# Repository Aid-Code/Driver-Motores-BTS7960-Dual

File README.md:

# TitanCore 7960: Driver BTS7960 Dual Channel Custom
#### Buenas! Soy Aiden, y les quise escribir un pequeño texto para comentarles de este desarrollo que hice para mi robot y para la comunidad!

## Origen
La idea inicialmente empezó porque utilizaba un Monster Shield (VNH2SP30) que no suele ser tan fácil de conseguir, y quizás si se consigue es caro, por lo que necesitaba conseguir una alternativa a este driver de motores para mi robot Sumo.  
De ahí empecé a buscar como funcionaba un **Puente H**, que componentes se usaban, que transistores usar y por qué.   
Como primer acercamiento armé un Puente H con transistores mosfet en una placa experimental, usando gate drivers, que milagrosamente funcionó (después de revisar 50 veces mis dudosas soldaduras a las 5 A.M), pero cuando hice un primer diseño de la PCB, me di cuenta que no era lo suficientemente eficiente en espacio.
No importaba cuantos componentes SMD usara, era imposible reducirla.   
Más adelante, después de un tiempo de buscar (y charlar con mi LLM de confianza) encontré que existían encapsulados que integraban dos transistores "en uno". 
A todo esto, yo ya conocía el módulo comercial del BTS7960, pero me parecía una placa gigante (con un disipador gigante) para el uso que yo le quería dar. En esta parte de mi investigación descubrí que los BTS7960 eran esos peculiares encapsulados que integraban "dos transistores en uno". Por lo que dije PERFECTO, LOS COMPRO; LOS DESUELDO; ARMO MI PLACA!  
Dicho y hecho, acá estamos!

## Funcionamiento
La dinamica de este driver de motores es un poco distinta a lo habitual, comparandola con un Monster Shield o un L298n.  
Los pines son:
- GND
- VCC --> Voltaje lógico de 3.3v a 5v
- EN_1 --> Habilita el paso de corriente al Canal 1 (Opcional conectarlo a un pin, puede ir a VCC)
- EN_2 --> Habilita el paso de corriente al Canal 2 (Opcional conectarlo a un pin, puede ir a VCC)
- PWM_A --> Señal PWM del Canal 1 en una dirección
- PWM_B --> Señal PWM del Canal 1 en dirección contraria
- PWM_C --> Señal PWM del Canal 2 en una dirección
- PWM_D --> Señal PWM del Canal 2 en dirección contraria

- VS --> Voltaje de alimentación y salida a los motores de 6v a 28v (**Aprox. basado en la datasheet del BTS7960**)

## Puesto a prueba
Hasta ahora los parametros con los que puse a prueba el funcionamiento del driver son:  
- VCC: 5v
- VS: ~15v

La idea es utilizarlo a 24v con motores que podrían llegar a consumir 11,2A por canal. Cuando lo pruebe y confirme que no explota lo comento!

## Licencia y Uso Comercial
*Este proyecto está licenciado bajo* **Creative Commons Atribución-NoComercial-CompartirIgual 4.0 Internacional (CC BY-NC-SA 4.0)**. Consulta el archivo [LICENSE](LICENSE) para más detalles.
- *Puedes clonar, fabricar, estudiar y modificar este diseño libremente para proyectos personales, educativos o de competencia.*
- *Queda terminantemente prohibida la comercialización, venta directa o integración comercial de este diseño sin autorización previa.*
- Para consultas comerciales o adquisición de módulos ensamblados, contactar a: aiden.maidp@gmail.com

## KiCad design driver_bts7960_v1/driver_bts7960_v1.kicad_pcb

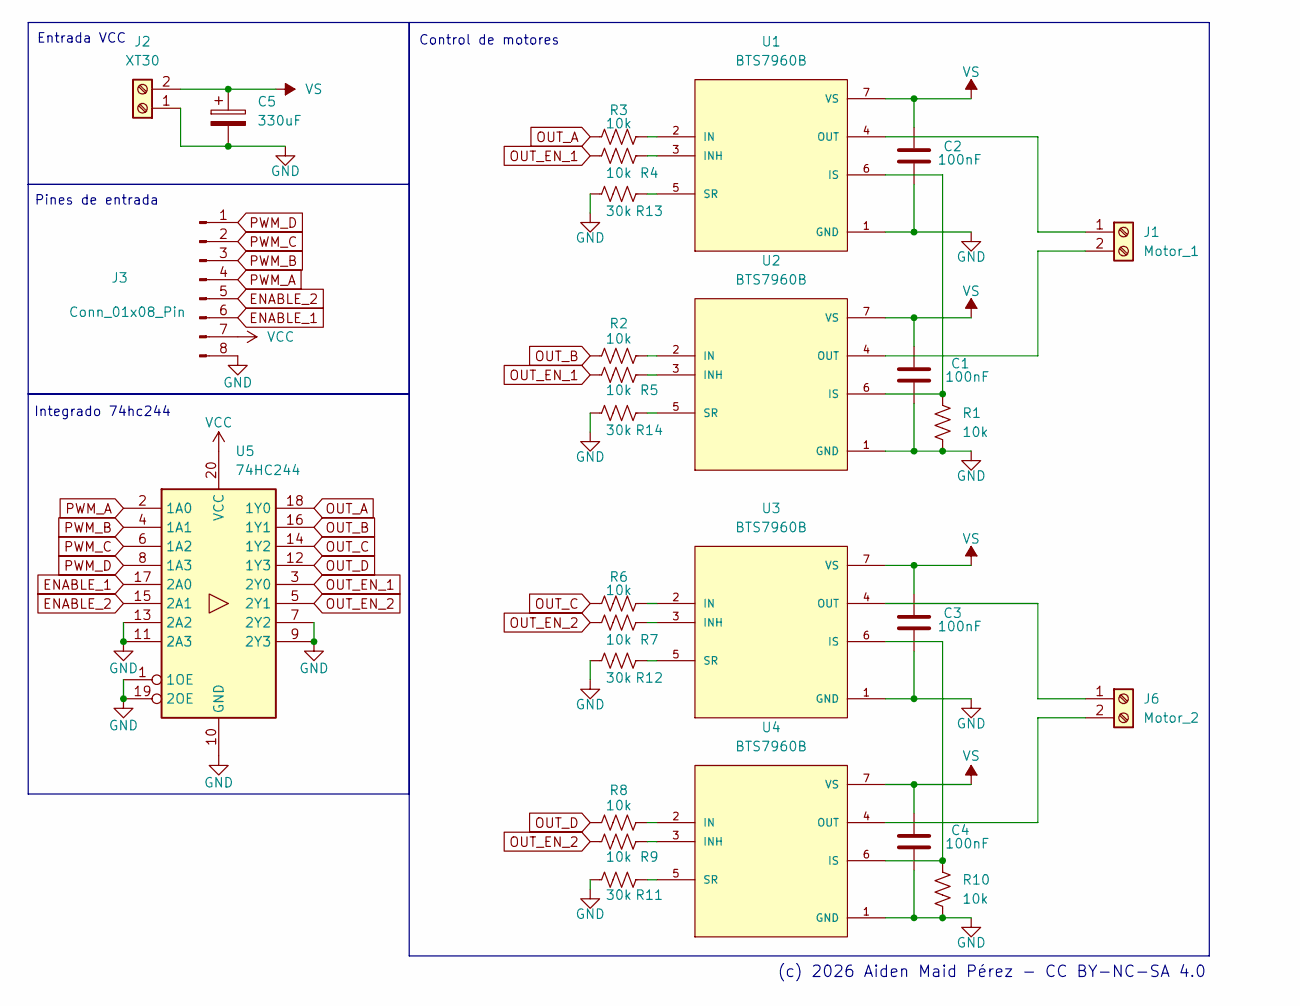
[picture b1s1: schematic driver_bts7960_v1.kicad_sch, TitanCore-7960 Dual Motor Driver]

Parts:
C1, C2, C3, C4: 100nF; C_0805_2012Metric_Pad1.18x1.45mm_HandSolder
C5: 330uF; CP_Radial_D8.0mm_P5.00mm
J1: Motor_1; AMASS_XT30U-F_1x02_P5.0mm_Vertical
J2: XT30; AMASS_XT30U-F_1x02_P5.0mm_Vertical
J3: Conn_01x08_Pin; PinHeader_1x08_P2.54mm_Vertical
J6: Motor_2; AMASS_XT30U-F_1x02_P5.0mm_Vertical
R1, R2, R3, R4, R5, R6, R7, R8, R9, R10: 10k; R_0805_2012Metric_Pad1.20x1.40mm_HandSolder
R11, R12, R13, R14: 30k; R_0805_2012Metric_Pad1.20x1.40mm_HandSolder
U1, U2, U3, U4: BTS7960B; BTS7960B_DPAK127P1490X440-8N; PARTREV 1.1
U5: 74HC244; SOIC127P1032X265-20N

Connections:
ENABLE_1: J3.6, U5.17 (2A0)
ENABLE_2: J3.5, U5.15 (2A1)
GND: C1.2, C2.2, C3.2, C4.2, C5.2, J2.1, J3.8, R1.2, R10.2, R11.2, R12.2, R13.2, R14.2, U1.1 (GND), U2.1 (GND), U3.1 (GND), U4.1 (GND), U5.1 (1OE), U5.7 (2Y2), U5.9 (2Y3), U5.10 (GND), U5.11 (2A3), U5.13 (2A2), U5.19 (2OE)
unnamed: J1.1, U1.4 (OUT), U1.8 (OUT)
unnamed: J1.2, U2.4 (OUT), U2.8 (OUT)
unnamed: J6.1, U3.4 (OUT), U3.8 (OUT)
unnamed: J6.2, U4.4 (OUT), U4.8 (OUT)
unnamed: R3.1, U1.2 (IN)
unnamed: R4.1, U1.3 (INH)
unnamed: R1.1, U1.6 (IS), U2.6 (IS)
unnamed: R13.1, U1.5 (SR)
unnamed: R2.1, U2.2 (IN)
unnamed: R5.1, U2.3 (INH)
unnamed: R14.1, U2.5 (SR)
unnamed: R6.1, U3.2 (IN)
unnamed: R7.1, U3.3 (INH)
unnamed: R10.1, U3.6 (IS), U4.6 (IS)
unnamed: R12.1, U3.5 (SR)
unnamed: R8.1, U4.2 (IN)
unnamed: R9.1, U4.3 (INH)
unnamed: R11.1, U4.5 (SR)
OUT_A: R3.2, U5.18 (1Y0)
OUT_B: R2.2, U5.16 (1Y1)
OUT_C: R6.2, U5.14 (1Y2)
OUT_D: R8.2, U5.12 (1Y3)
OUT_EN_1: R4.2, R5.2, U5.3 (2Y0)
OUT_EN_2: R7.2, R9.2, U5.5 (2Y1)
PWM_A: J3.4, U5.2 (1A0)
PWM_B: J3.3, U5.4 (1A1)
PWM_C: J3.2, U5.6 (1A2)
PWM_D: J3.1, U5.8 (1A3)
VCC: J3.7, U5.20 (VCC)
VS: C1.1, C2.1, C3.1, C4.1, C5.1, J2.2, U1.7 (VS), U2.7 (VS), U3.7 (VS), U4.7 (VS)

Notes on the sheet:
Entrada VCC
Pines de entrada
Integrado 74hc244
Control de motores
(c) 2026 Aiden Maid Pérez - CC BY-NC-SA 4.0

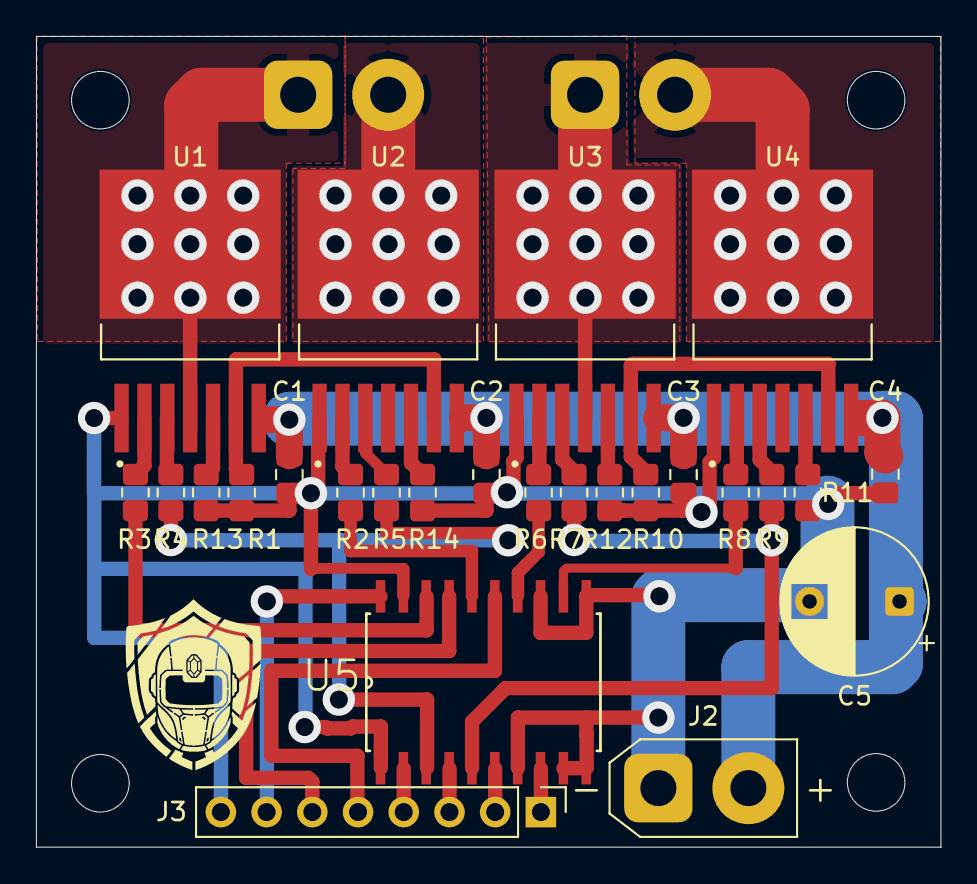
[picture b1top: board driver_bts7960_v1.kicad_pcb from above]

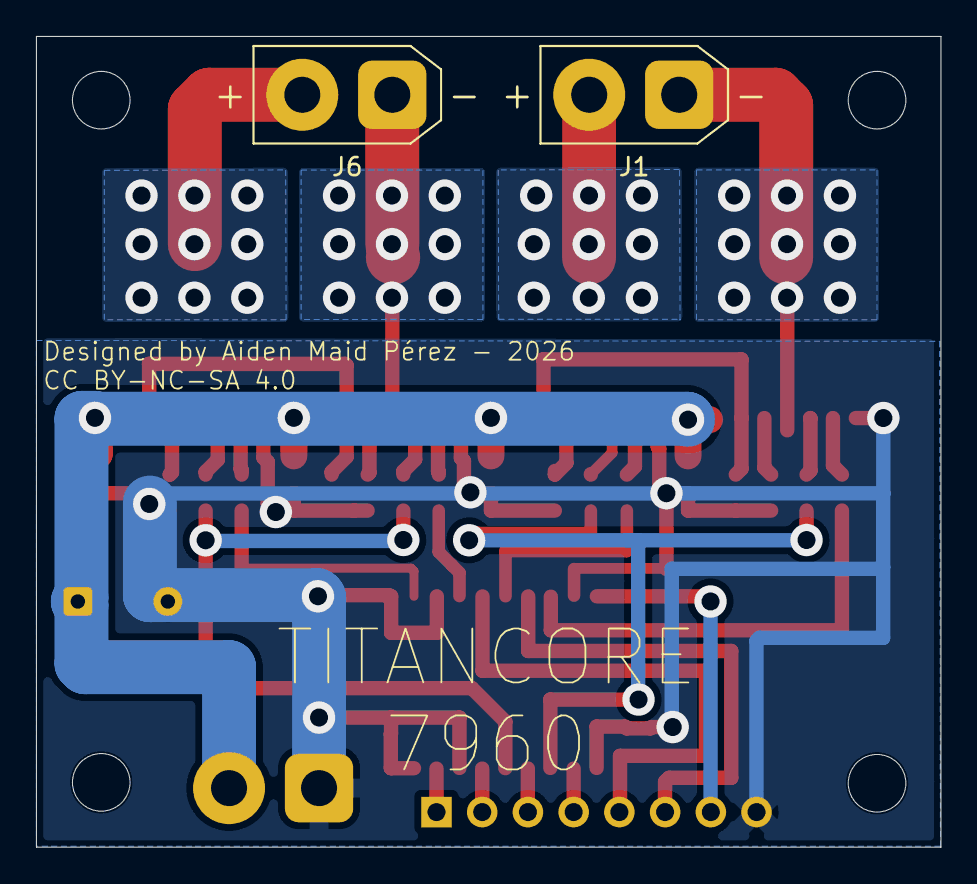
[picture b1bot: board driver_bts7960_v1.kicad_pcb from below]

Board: 2 copper layers, 50.3 x 45.0 mm, 28 parts (2 on the bottom side), 33 nets.

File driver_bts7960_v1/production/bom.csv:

Designator,Footprint,Quantity,Value,LCSC Part #
"C1, C2, C3, C4",0805,4,100nF,
C5,CP_Radial_D8.0mm_P5.00mm,1,330uF,
J1,AMASS_XT30U-F_1x02_P5.0mm_Vertical,1,Motor_1,
J2,AMASS_XT30U-F_1x02_P5.0mm_Vertical,1,XT30,
J3,PinHeader_1x08_P2.54mm_Vertical,1,Conn_01x08_Pin,
J6,AMASS_XT30U-F_1x02_P5.0mm_Vertical,1,Motor_2,
"R1, R10, R2, R3, R4, R5, R6, R7, R8, R9",0805,10,10k,
"R11, R12, R13, R14",0805,4,30k,
"U1, U2, U3, U4",BTS7960B_DPAK127P1490X440-8N,4,BTS7960B,
U5,SOIC127P1032X265-20N,1,74HC244,

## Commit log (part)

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2025-12-22 driver v1
2025-12-22 driver bts7960 v1
2025-12-23 driver bts7960 v2
2026-05-12 v2 terminado con 74hc244
2026-06-06 footprint 74hc244 corregido

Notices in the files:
driver_bts7960_v1/driver_bts7960_v1.kicad_sch:
Licensed under CC BY-NC-SA 4.0
